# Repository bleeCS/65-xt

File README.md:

# 65-xt
65 percent pcb with left function columns

## Renders
Renders generated using [tracespace.io](https://tracespace.io/).

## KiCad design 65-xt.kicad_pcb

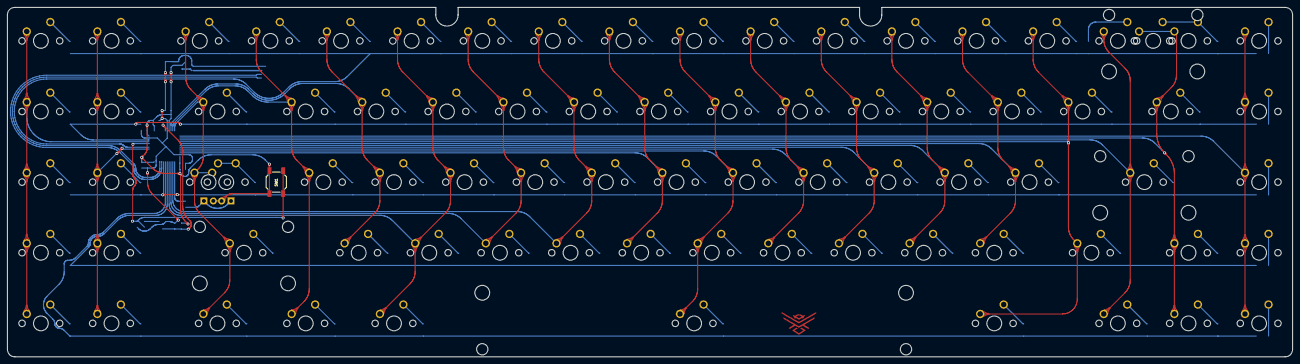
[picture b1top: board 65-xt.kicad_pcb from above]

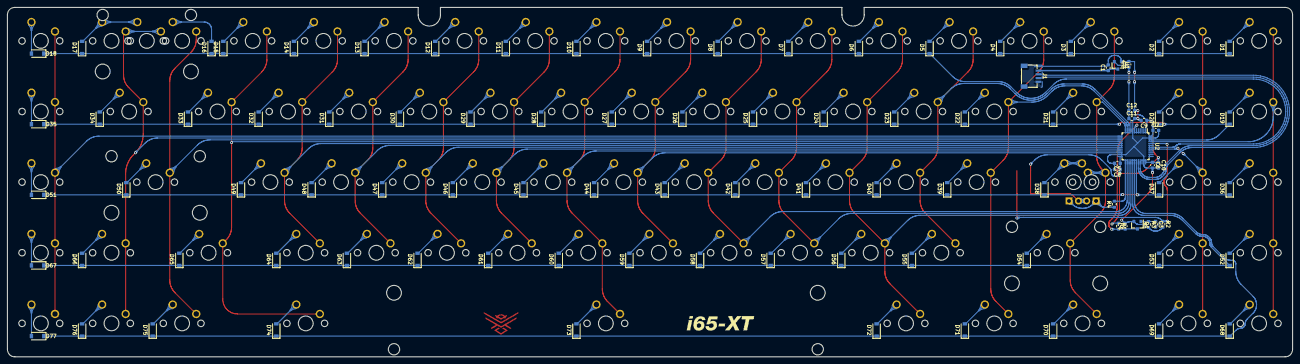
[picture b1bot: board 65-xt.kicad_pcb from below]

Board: 2 copper layers, 346.7 x 94.3 mm, 177 parts (97 on the bottom side), 110 nets.

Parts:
C1, C2, C12: 1uF; C_0603_1608Metric
C3, C8, C10: 4.7uF; C_0603_1608Metric
C4: 470nF; C_0603_1608Metric
C5, C6, C7, C9: 100nF; C_0603_1608Metric
C11: 10nF; C_0603_1608Metric
D1, D2, D3, D4, D5, D6, D7, D8, D9, D10, D11, D12, D13, D14, D15, D16, D17, D18, D19, D20, D21, D22, D23, D24, D25, D26, D27, D28, D29, D30, D31, D32, D33, D34, D35, D36, D37, D38, D39, D40, D41, D42, D43, D44, D45, D46, D47, D48, D49, D50, D51, D52, D53, D54, D55, D56, D57, D58, D59, D60, D61, D62, D63, D64, D65, D66, D67, D68, D69, D70, D71, D72, D73, D74, D75, D76, D77: D_Small; D_SOD-123
J1: Conn_01x04; JST-SR-4
MX1, MX2, MX3, MX4, MX5, MX6, MX7, MX8, MX9, MX10, MX11, MX12, MX13, MX14, MX15, MX16, MX17, MX19, MX20, MX21, MX23, MX24, MX25, MX26, MX27, MX28, MX29, MX30, MX31, MX32, MX33, MX34, MX36, MX37, MX38, MX41, MX42, MX43, MX44, MX45, MX46, MX47, MX48, MX49, MX50, MX51, MX53, MX54, MX55, MX57, MX58, MX59, MX60, MX61, MX62, MX63, MX64, MX65, MX66, MX68, MX69, MX70, MX71, MX73, MX77, MX78, MX79: MX-NoLED; MXOnly-1U-NoLED
MX18: MX-NoLED; MXOnly-2U-NoLED
MX22, MX35, MX72, MX74, MX76: MX-NoLED; MXOnly-1.5U-NoLED
MX39: MX-LED; MXOnly-1.25U-FLIPPED
MX40: MX-LED; MXOnly-1.75U
MX52, MX56: MX-NoLED; MXOnly-2.25U-NoLED
MX67: MX-NoLED; MXOnly-1.75U-NoLED
MX75: MX-NoLED; MXOnly-7U-ReversedStabilizers-NoLED
Q1: 2N7002; SOT-23
R1, R2: 10k; R_0603_1608Metric
R3: 100k; R_0603_1608Metric
R4: 1k; R_0603_1608Metric
SW1: SW_Push; K2-1187SQ-A4SW-06
U1: MCP1700-3302E_SOT23; SOT-23
U2: STM32F072CBT6; LQFP-48_7x7mm_P0.5mm

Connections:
+3V3: C2.1, C5.1, C6.1, C7.1, C8.1, C9.1, C10.1, C11.1, C12.1, MX39.3, MX40.3, R1.1, SW1.2, U1.2, U2.1, U2.9, U2.24, U2.36, U2.48
+5V: C1.1, J1.1, U1.3
BOOT0: C3.2, R2.1, SW1.1, U2.44
CapsLED: R4.2, U2.25
Col0: MX1.1, MX20.1, MX37.1, MX54.1, MX70.1, U2.45
Col1: MX2.1, MX21.1, MX38.1, MX55.1, MX71.1, U2.41
Col2: MX3.1, MX22.1, MX39.1, MX40.1, MX56.1, MX72.1, U2.12
Col3: MX4.1, MX23.1, MX41.1, MX73.1, U2.11
Col4: MX5.1, MX24.1, MX42.1, MX57.1, U2.10
Col5: MX6.1, MX25.1, MX43.1, MX58.1, MX74.1, U2.28
Col6: MX7.1, MX26.1, MX44.1, MX59.1, U2.27
Col7: MX8.1, MX27.1, MX45.1, MX60.1, U2.26
Col8: MX9.1, MX28.1, MX46.1, MX61.1, U2.22
Col9: MX10.1, MX29.1, MX47.1, MX62.1, MX75.1, U2.21
Col10: MX11.1, MX30.1, MX48.1, MX63.1, U2.20
Col11: MX12.1, MX31.1, MX49.1, MX64.1, U2.19
Col12: MX13.1, MX32.1, MX50.1, MX65.1, U2.18
Col13: MX14.1, MX33.1, MX51.1, MX66.1, U2.17
Col14: MX15.1, MX34.1, MX67.1, MX76.1, U2.16
Col15: MX16.1, MX52.1, MX77.1, U2.15
Col16: MX17.1, MX18.1, MX35.1, MX68.1, MX78.1, U2.14
Col17: MX19.1, MX36.1, MX53.1, MX69.1, MX79.1, U2.13
D+: J1.3, U2.33
D-: J1.2, U2.32
GND: C1.2, C2.2, C4.2, C5.2, C6.2, C7.2, C8.2, C9.2, C10.2, C11.2, C12.2, J1.4, Q1.2, R2.2, R3.2, U1.1, U2.8, U2.23, U2.35, U2.47
NRST: C4.1, Q1.3, R1.2, U2.7
unnamed: C3.1, Q1.1, R3.1
unnamed: D1.2, MX1.2
unnamed: D2.2, MX2.2
unnamed: D3.2, MX3.2
unnamed: D4.2, MX4.2
unnamed: D5.2, MX5.2
unnamed: D6.2, MX6.2
unnamed: D7.2, MX7.2
unnamed: D8.2, MX8.2
unnamed: D9.2, MX9.2
unnamed: D10.2, MX10.2
unnamed: D11.2, MX11.2
unnamed: D12.2, MX12.2
unnamed: D13.2, MX13.2
unnamed: D14.2, MX14.2
unnamed: D15.2, MX15.2
unnamed: D16.2, MX16.2
unnamed: D17.2, MX17.2, MX18.2
unnamed: D18.2, MX19.2
unnamed: D19.2, MX20.2
unnamed: D20.2, MX21.2
unnamed: D21.2, MX22.2
unnamed: D22.2, MX23.2
unnamed: D23.2, MX24.2
unnamed: D24.2, MX25.2
unnamed: D25.2, MX26.2
unnamed: D26.2, MX27.2
unnamed: D27.2, MX28.2
unnamed: D28.2, MX29.2
unnamed: D29.2, MX30.2
unnamed: D30.2, MX31.2
unnamed: D31.2, MX32.2
unnamed: D32.2, MX33.2
unnamed: D33.2, MX34.2
unnamed: D34.2, MX35.2
unnamed: D35.2, MX36.2
unnamed: D36.2, MX37.2
unnamed: D37.2, MX38.2
unnamed: D38.2, MX39.2, MX40.2
unnamed: D39.2, MX41.2
unnamed: D40.2, MX42.2
unnamed: D41.2, MX43.2
unnamed: D42.2, MX44.2
unnamed: D43.2, MX45.2
unnamed: D44.2, MX46.2
unnamed: D45.2, MX47.2
unnamed: D46.2, MX48.2
unnamed: D47.2, MX49.2
unnamed: D48.2, MX50.2
unnamed: D49.2, MX51.2
unnamed: D50.2, MX52.2
unnamed: D51.2, MX53.2
unnamed: D52.2, MX54.2
unnamed: D53.2, MX55.2
unnamed: D54.2, MX56.2
unnamed: D55.2, MX57.2
unnamed: D56.2, MX58.2
unnamed: D57.2, MX59.2
unnamed: D58.2, MX60.2
unnamed: D59.2, MX61.2
unnamed: D60.2, MX62.2
unnamed: D61.2, MX63.2
unnamed: D62.2, MX64.2
unnamed: D63.2, MX65.2
unnamed: D64.2, MX66.2
unnamed: D65.2, MX67.2
unnamed: D66.2, MX68.2
unnamed: D67.2, MX69.2
unnamed: D68.2, MX70.2
unnamed: D69.2, MX71.2
unnamed: D70.2, MX72.2
unnamed: D71.2, MX73.2
unnamed: D72.2, MX74.2
unnamed: D73.2, MX75.2
unnamed: D74.2, MX76.2
unnamed: D75.2, MX77.2
unnamed: D76.2, MX78.2
unnamed: D77.2, MX79.2
unnamed: MX39.4, MX40.4, R4.1
Row0: D1.1, D2.1, D3.1, D4.1, D5.1, D6.1, D7.1, D8.1, D9.1, D10.1, D11.1, D12.1, D13.1, D14.1, D15.1, D16.1, D17.1, D18.1, U2.42
Row1: D19.1, D20.1, D21.1, D22.1, D23.1, D24.1, D25.1, D26.1, D27.1, D28.1, D29.1, D30.1, D31.1, D32.1, D33.1, D34.1, D35.1, U2.46
Row2: D36.1, D37.1, D38.1, D39.1, D40.1, D41.1, D42.1, D43.1, D44.1, D45.1, D46.1, D47.1, D48.1, D49.1, D50.1, D51.1, U2.31
Row3: D52.1, D53.1, D54.1, D55.1, D56.1, D57.1, D58.1, D59.1, D60.1, D61.1, D62.1, D63.1, D64.1, D65.1, D66.1, D67.1, U2.29
Row4: D68.1, D69.1, D70.1, D71.1, D72.1, D73.1, D74.1, D75.1, D76.1, D77.1, U2.30

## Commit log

2020-10-24 initializing kicad project
2020-10-24 add project submodules
2020-10-24 add footprint libraries
2020-10-25 add submodule for reset switch, main schematic for mcu, switch matrix
2020-10-25 place components and route
2020-10-26 remove submodule, update footprints
2020-10-26 moving things around
2020-10-28 adjust reset switch position, add tear drops, add board art
2020-10-28 update edge cuts
2020-10-31 add tracespace renders and update readme
2020-12-26 updating reset/boot R and C values
